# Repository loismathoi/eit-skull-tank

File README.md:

> [!WARNING]
> Work in progress. Incomplete and subject to change.

# Electrical Impedance Tomography Skull Phantom

16-electrode EIT system and FDM-printed head phantom, built to see how a skull analogue interacts with EIT imaging and ischemia detection.

## Goals
- How accurate is EIT on a 3D-printed, quasi-2D tank?
- How does the inclusion of a skull-ring impact measurement accuracy?
- Can a neural network improve accuracy and detectable inclusion size compared to GREIT?

## Repository

- [hardware/](hardware/): PCB and tank design files.
- [firmware/](firmware/): code that runs on the PCB.
- [sim/](sim/): simulation of the phantom.
- [img/](img/): images.
- [environment.yml](environment.yml): Python environment.

## System

- CALVA: the PCB, details in [hardware/README.md](hardware/README.md).
- Tank: 3D-printed, TODO.

## Status

- Done: PCB rev 1.0 designed and fabricated.
- Done: stock firmware builds, not flashed yet.
- Done: basic simulation of the tank with GREIT reconstruction (See  [here](/img/sim-greit-ring.png)).
- TODO: PCB assembly and bring-up.
- TODO: tank design and printing.
- Planning: data acquisition.
- Planning: neural network.

## Credits

- [CN0565](https://www.analog.com/en/resources/reference-designs/circuits-from-the-lab/CN0565.html), [EVAL-ADICUP3029](https://www.analog.com/en/resources/evaluation-hardware-and-software/evaluation-boards-kits/eval-adicup3029.html), [no-OS](https://github.com/analogdevicesinc/no-OS), [pyEIT](https://github.com/eitcom/pyEIT)

## License

- [hardware/](hardware/): CERN-OHL-P v2, see [hardware/LICENSE](hardware/LICENSE).
- [firmware/no-OS](https://github.com/loismathoi/no-OS/tree/calva): its own licenses, see [firmware/no-OS/COPYING](https://github.com/loismathoi/no-OS/blob/calva/COPYING).
- Everything else: MIT, see [LICENSE](LICENSE).

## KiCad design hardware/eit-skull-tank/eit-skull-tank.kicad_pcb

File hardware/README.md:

# HARDWARE

## CALVA

*Bare PCB*

- 16-electrode EIT board, rev 1.0, 4-layer, 100 x 51 mm.
- Electrode side isolated from the USB side, following CN0565.

## Based on

- [CN0565](https://www.analog.com/en/resources/reference-designs/circuits-from-the-lab/CN0565.html): AFE, mux, isolation, isolated power.
- [EVAL-ADICUP3029](https://www.analog.com/en/resources/evaluation-hardware-and-software/evaluation-boards-kits/eval-adicup3029.html): MCU, clocks, SWD, LEDs.

## Files

- [eit-skull-tank/](eit-skull-tank/): KiCad 10 project.
- [eit-skull-tank.pdf](eit-skull-tank.pdf): schematic.
- Sheets: [usb_power](eit-skull-tank/usb_power.kicad_sch), [mcu](eit-skull-tank/mcu.kicad_sch), [iso_power](eit-skull-tank/iso_power.kicad_sch), [iso_comm](eit-skull-tank/iso_comm.kicad_sch), [afe](eit-skull-tank/afe.kicad_sch), [mux](eit-skull-tank/mux.kicad_sch).

## Fabrication

- AISLER, 4-layer, 1.6 mm, ENIG, exported with the AISLER KiCad plugin.
- Stencil and hot plate reflow.

## Tank
### TODO

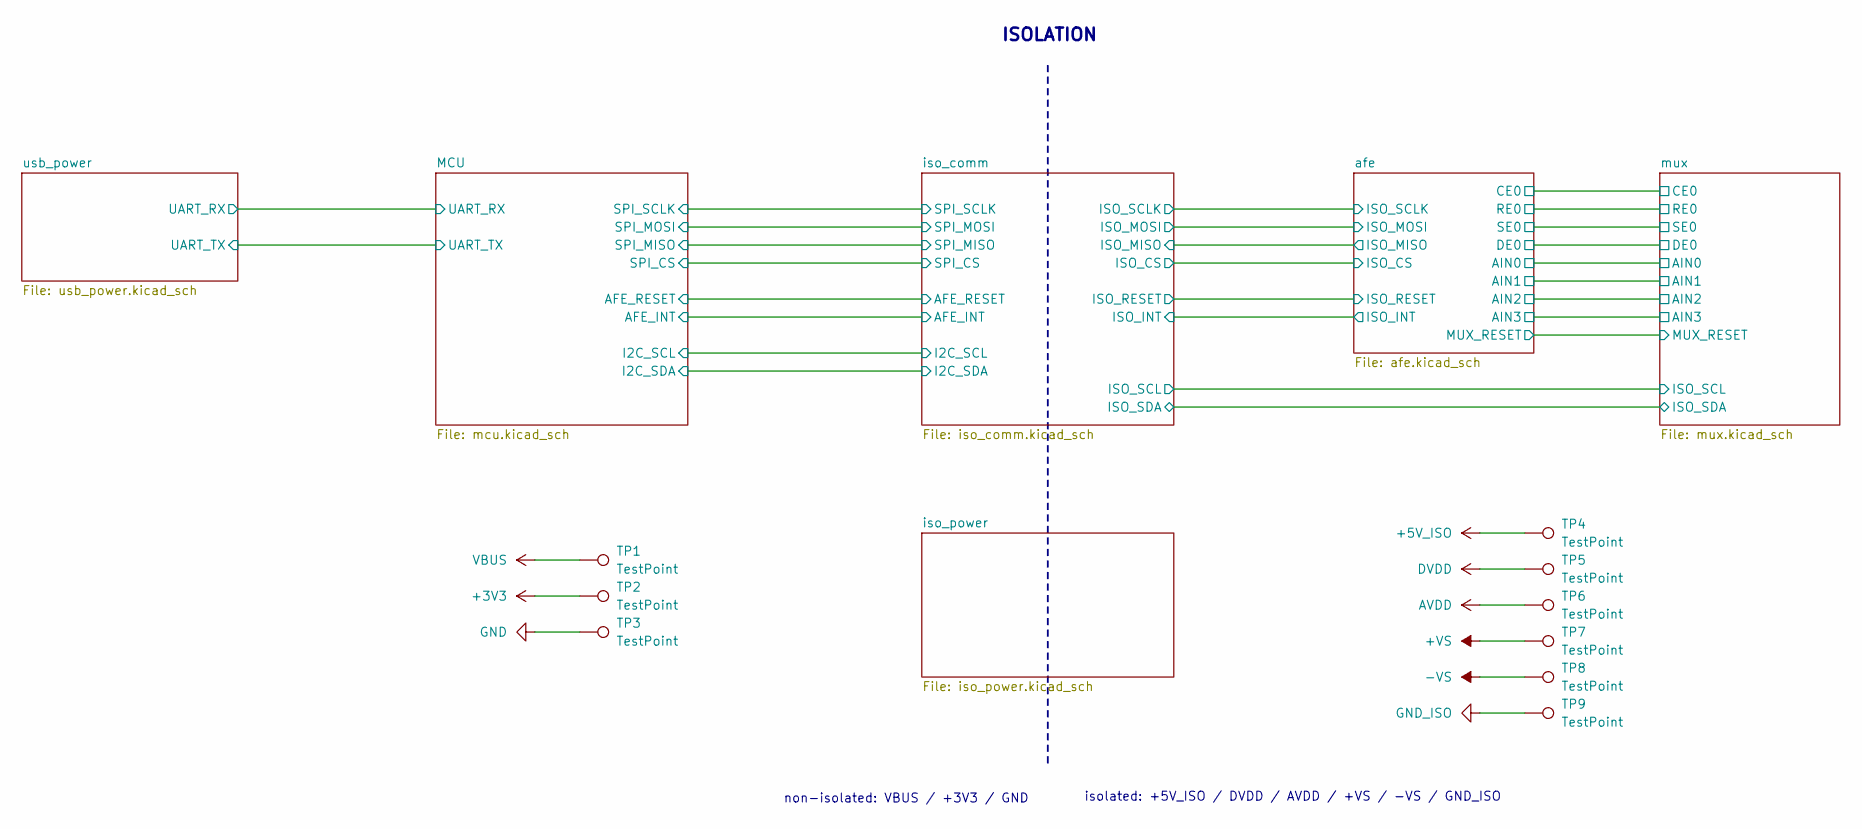
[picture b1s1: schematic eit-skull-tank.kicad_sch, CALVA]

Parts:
TP1, TP2, TP3, TP4, TP5, TP6, TP7, TP8, TP9: TestPoint; TestPoint_Pad_D1.5mm

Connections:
+3V3: TP2.1 (1_1); also elsewhere on the board
+5V_ISO: TP4.1 (1_1); also elsewhere on the board
+VS: TP7.1 (1_1); also elsewhere on the board
-VS: TP8.1 (1_1); also elsewhere on the board
AVDD: TP6.1 (1_1); also elsewhere on the board
DVDD: TP5.1 (1_1); also elsewhere on the board
GND: TP3.1 (1_1); also elsewhere on the board
GND_ISO: TP9.1 (1_1); also elsewhere on the board
VBUS: TP1.1 (1_1); also elsewhere on the board

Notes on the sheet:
isolated: +5V_ISO / DVDD / AVDD / +VS / -VS / GND_ISO
ISOLATION
non-isolated: VBUS / +3V3 / GND

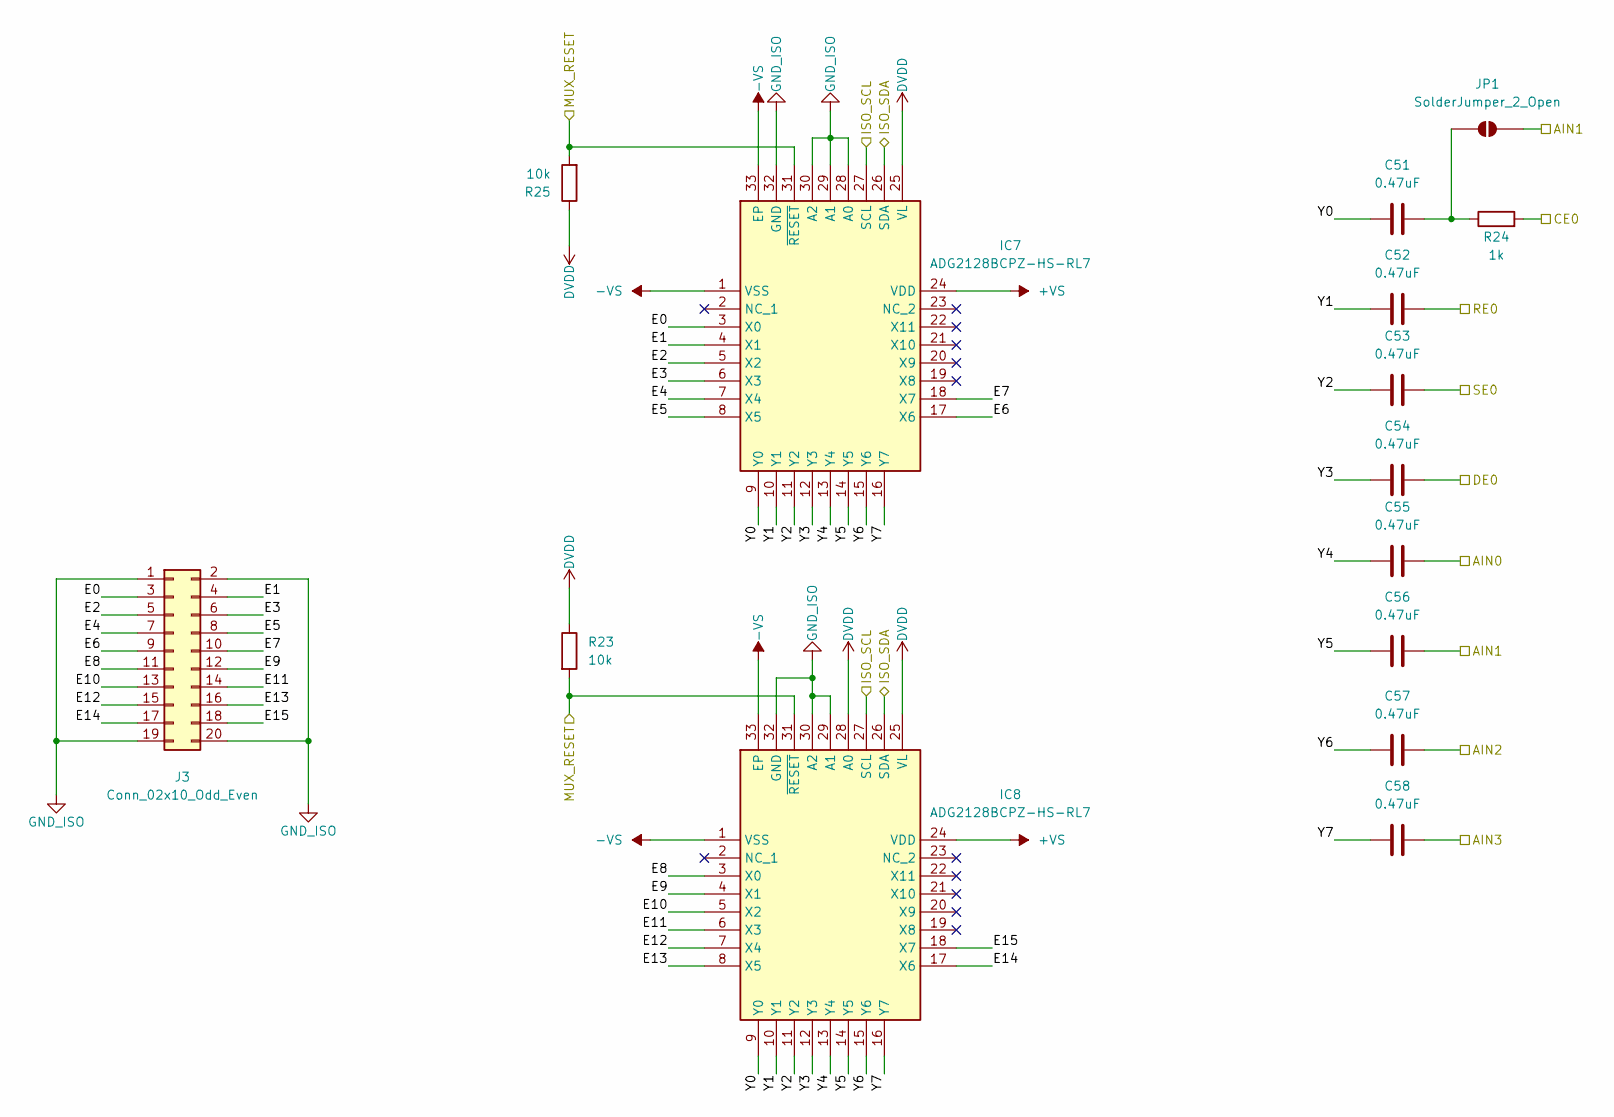
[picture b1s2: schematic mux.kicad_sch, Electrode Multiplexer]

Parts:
C51, C52, C53, C54, C55, C56, C57, C58: 0.47uF; C_0805_2012Metric; MPN CL21B474KAFNNNE
IC7, IC8: ADG2128BCPZ-HS-RL7; LFCSP-32-1EP_5x5mm_P0.5mm_EP3.25x3.25mm; MPN ADG2128BCPZ-HS-RL7
J3: Conn_02x10_Odd_Even; IDC-Header_2x10_P2.54mm_Vertical; MPN 61202021621
JP1: SolderJumper_2_Open; SolderJumper-2_P1.3mm_Open_RoundedPad1.0x1.5mm
R23, R25: 10k; R_0805_2012Metric; MPN RC0805FR-0710KL
R24: 1k; R_0805_2012Metric; MPN RC0805FR-071KL

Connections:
+VS: IC7.24 (VDD), IC8.24 (VDD); also elsewhere on the board
-VS: IC7.1 (VSS), IC7.33 (EP), IC8.1 (VSS), IC8.33 (EP); also elsewhere on the board
/afe/AIN0: C55.2; also elsewhere on the board
/afe/AIN1: C56.2, JP1.2 (B); also elsewhere on the board
/afe/AIN2: C57.2; also elsewhere on the board
/afe/AIN3: C58.2; also elsewhere on the board
/afe/CE0: R24.2; also elsewhere on the board
/afe/DE0: C54.2; also elsewhere on the board
/afe/MUX_RESET: IC7.31 (~RESET), IC8.31 (~RESET), R23.2, R25.2; also elsewhere on the board
/afe/RE0: C52.2; also elsewhere on the board
/afe/SE0: C53.2; also elsewhere on the board
/iso_comm/ISO_SCL: IC7.27 (SCL), IC8.27 (SCL); also elsewhere on the board
/iso_comm/ISO_SDA: IC7.26 (SDA), IC8.26 (SDA); also elsewhere on the board
/mux/E0: IC7.3 (X0), J3.3
/mux/E1: IC7.4 (X1), J3.4
/mux/E2: IC7.5 (X2), J3.5
/mux/E3: IC7.6 (X3), J3.6
/mux/E4: IC7.7 (X4), J3.7
/mux/E5: IC7.8 (X5), J3.8
/mux/E6: IC7.17 (X6), J3.9
/mux/E7: IC7.18 (X7), J3.10
/mux/E8: IC8.3 (X0), J3.11
/mux/E9: IC8.4 (X1), J3.12
/mux/E10: IC8.5 (X2), J3.13
/mux/E11: IC8.6 (X3), J3.14
/mux/E12: IC8.7 (X4), J3.15
/mux/E13: IC8.8 (X5), J3.16
/mux/E14: IC8.17 (X6), J3.17
/mux/E15: IC8.18 (X7), J3.18
/mux/Y0: C51.1, IC7.9 (Y0), IC8.9 (Y0)
/mux/Y1: C52.1, IC7.10 (Y1), IC8.10 (Y1)
/mux/Y2: C53.1, IC7.11 (Y2), IC8.11 (Y2)
/mux/Y3: C54.1, IC7.12 (Y3), IC8.12 (Y3)
/mux/Y4: C55.1, IC7.13 (Y4), IC8.13 (Y4)
/mux/Y5: C56.1, IC7.14 (Y5), IC8.14 (Y5)
/mux/Y6: C57.1, IC7.15 (Y6), IC8.15 (Y6)
/mux/Y7: C58.1, IC7.16 (Y7), IC8.16 (Y7)
DVDD: IC7.25 (VL), IC8.25 (VL), IC8.28 (A0), R23.1, R25.1; also elsewhere on the board
GND_ISO: IC7.28 (A0), IC7.29 (A1), IC7.30 (A2), IC7.32 (GND), IC8.29 (A1), IC8.30 (A2), IC8.32 (GND), J3.1, J3.2, J3.19, J3.20; also elsewhere on the board
unnamed: C51.2, JP1.1 (A), R24.1

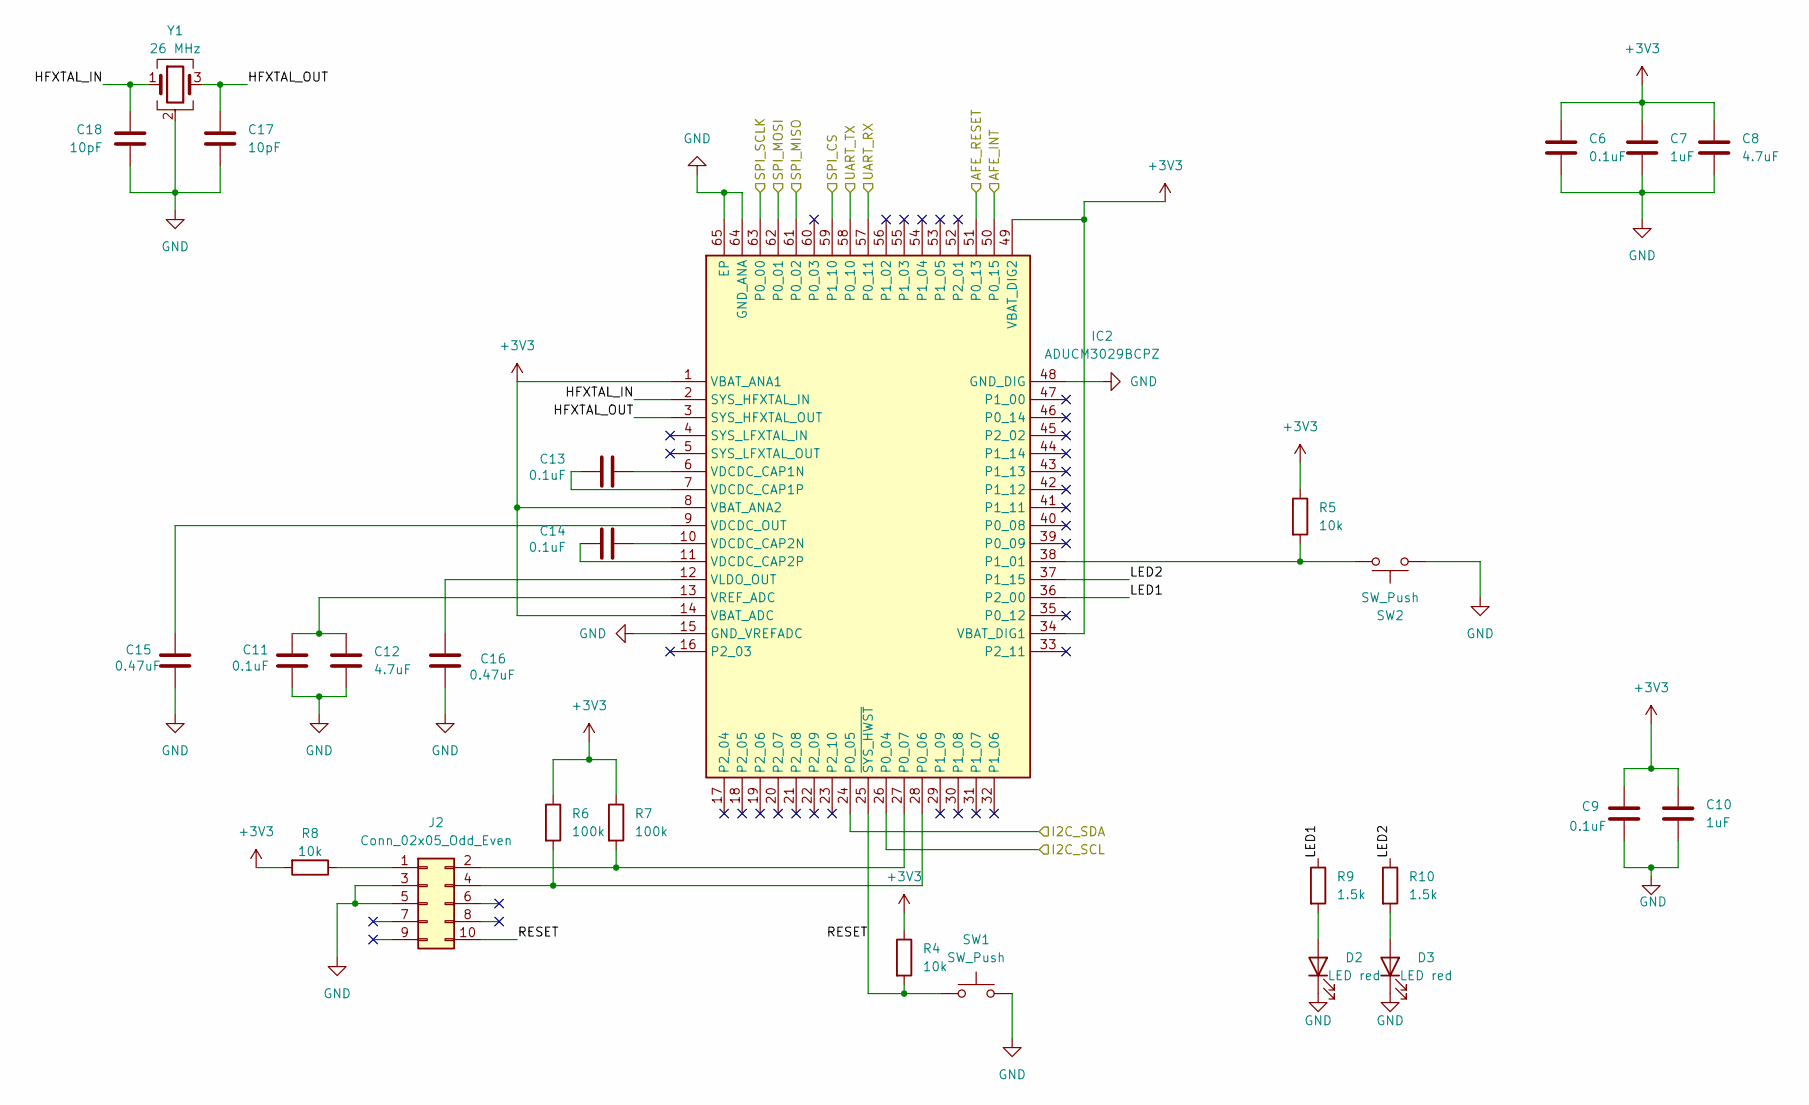
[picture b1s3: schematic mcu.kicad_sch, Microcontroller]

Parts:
C6, C9, C11, C13, C14: 0.1uF; C_0603_1608Metric; MPN CC0603KRX7R9BB104
C7, C10: 1uF; C_0603_1608Metric; MPN C1608X7R1E105K080AB
C8, C12: 4.7uF; C_0603_1608Metric; MPN CL10A475KA8NQNC
C15, C16: 0.47uF; C_0603_1608Metric; MPN GRM188R71C474KA88D
C17, C18: 10pF; C_0603_1608Metric; MPN CL10C100JB81PNC
D2, D3: LED red; LED_0805_2012Metric; MPN APT2012SURCK
IC2: ADUCM3029BCPZ; LFCSP-64-1EP_9x9mm_P0.5mm_EP4.6x4.6mm; MPN ADUCM3029BCPZ-R7
J2: Conn_02x05_Odd_Even; Samtec_FTSH-105-01-L-DV-K_2x05_P1.27mm; MPN FTSH-105-01-L-DV-K
R4, R5, R8: 10k; R_0805_2012Metric; MPN RC0805FR-0710KL
R6, R7: 100k; R_0805_2012Metric; MPN RC0805FR-07100KL
R9, R10: 1.5k; R_0805_2012Metric; MPN RC0805FR-071K5L
SW1, SW2: SW_Push; SW_SPST_PTS645Sx43SMTR92; MPN PTS645SM43SMTR92 LFS
Y1: 26 MHz; Crystal_SMD_3225-4Pin_3.2x2.5mm; MPN ECS-260-8-33-RWY-TR

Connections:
+3V3: C6.1, C7.1, C8.1, C9.1, C10.1, IC2.1 (VBAT_ANA1), IC2.8 (VBAT_ANA2), IC2.14 (VBAT_ADC), IC2.34 (VBAT_DIG1), IC2.49 (VBAT_DIG2), R4.1, R5.1, R6.1, R7.1, R8.2; also elsewhere on the board
/MCU/AFE_INT: IC2.50 (P0_15); also elsewhere on the board
/MCU/AFE_RESET: IC2.51 (P0_13); also elsewhere on the board
/MCU/HFXTAL_IN: C18.1, IC2.2 (SYS_HFXTAL_IN), Y1.1
/MCU/HFXTAL_OUT: C17.1, IC2.3 (SYS_HFXTAL_OUT), Y1.3
/MCU/I2C_SCL: IC2.26 (P0_04); also elsewhere on the board
/MCU/I2C_SDA: IC2.24 (P0_05); also elsewhere on the board
/MCU/LED1: IC2.36 (P2_00), R9.1
/MCU/LED2: IC2.37 (P1_15), R10.1
/MCU/RESET: IC2.25 (~SYS_HWST), J2.10, R4.2, SW1.1
/MCU/SPI_CS: IC2.59 (P1_10); also elsewhere on the board
/MCU/SPI_MISO: IC2.61 (P0_02); also elsewhere on the board
/MCU/SPI_MOSI: IC2.62 (P0_01); also elsewhere on the board
/MCU/SPI_SCLK: IC2.63 (P0_00); also elsewhere on the board
/MCU/UART_RX: IC2.57 (P0_11); also elsewhere on the board
/MCU/UART_TX: IC2.58 (P0_10); also elsewhere on the board
GND: C6.2, C7.2, C8.2, C9.2, C10.2, C11.2, C12.2, C15.2, C16.2, C17.2, C18.2, D2.1 (K), D3.1 (K), IC2.15 (GND_VREFADC), IC2.48 (GND_DIG), IC2.64 (GND_ANA), IC2.65 (EP), J2.3, J2.5, SW1.2, SW2.1, Y1.2 (G), Y1.4 (G); also elsewhere on the board
unnamed: D2.2 (A), R9.2
unnamed: D3.2 (A), R10.2
unnamed: IC2.28 (P0_06), J2.4, R6.2
unnamed: IC2.27 (P0_07), J2.2, R7.2
unnamed: IC2.38 (P1_01), R5.2, SW2.2
unnamed: C13.1, IC2.6 (VDCDC_CAP1N)
unnamed: C13.2, IC2.7 (VDCDC_CAP1P)
unnamed: C14.1, IC2.10 (VDCDC_CAP2N)
unnamed: C14.2, IC2.11 (VDCDC_CAP2P)
unnamed: C15.1, IC2.9 (VDCDC_OUT)
unnamed: C16.1, IC2.12 (VLDO_OUT)
unnamed: C11.1, C12.1, IC2.13 (VREF_ADC)
unnamed: J2.1, R8.1

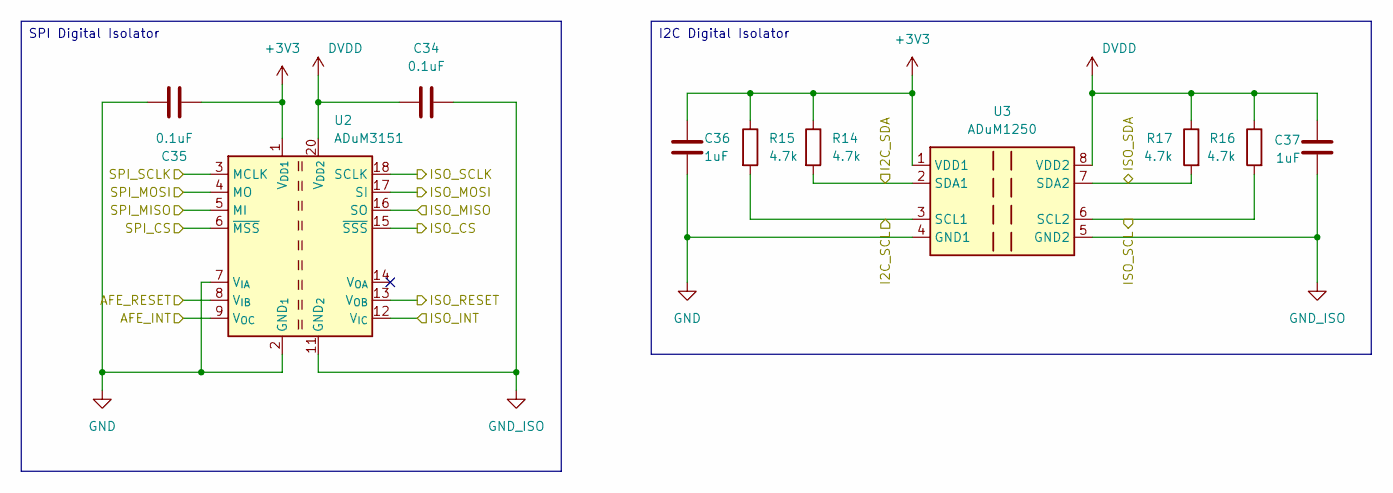
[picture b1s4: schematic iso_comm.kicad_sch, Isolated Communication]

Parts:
C34, C35: 0.1uF; C_0805_2012Metric; MPN CL21B104KBCNNNC
C36, C37: 1uF; C_0805_2012Metric; MPN C0805C105K5RACTU
R14, R15, R16, R17: 4.7k; R_0805_2012Metric; MPN RC0805FR-074K7L
U2: ADuM3151; SSOP-20_5.3x7.2mm_P0.65mm; MPN ADUM3151BRSZ
U3: ADuM1250; SOIC-8_3.9x4.9mm_P1.27mm; MPN ADUM1250ARZ

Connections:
+3V3: C35.2, C36.1, R14.1, R15.1, U2.1 (V_{DD1}), U3.1 (VDD1); also elsewhere on the board
/MCU/AFE_INT: U2.9 (V_{OC}); also elsewhere on the board
/MCU/AFE_RESET: U2.8 (V_{IB}); also elsewhere on the board
/MCU/I2C_SCL: R15.2, U3.3 (SCL1); also elsewhere on the board
/MCU/I2C_SDA: R14.2, U3.2 (SDA1); also elsewhere on the board
/MCU/SPI_CS: U2.6 (~MSS); also elsewhere on the board
/MCU/SPI_MISO: U2.5 (MI); also elsewhere on the board
/MCU/SPI_MOSI: U2.4 (MO); also elsewhere on the board
/MCU/SPI_SCLK: U2.3 (MCLK); also elsewhere on the board
/afe/ISO_CS: U2.15 (~SSS); also elsewhere on the board
/afe/ISO_INT: U2.12 (V_{IC}); also elsewhere on the board
/afe/ISO_MISO: U2.16 (SO); also elsewhere on the board
/afe/ISO_MOSI: U2.17 (SI); also elsewhere on the board
/afe/ISO_RESET: U2.13 (V_{OB}); also elsewhere on the board
/afe/ISO_SCLK: U2.18 (SCLK); also elsewhere on the board
/iso_comm/ISO_SCL: R16.2, U3.6 (SCL2); also elsewhere on the board
/iso_comm/ISO_SDA: R17.2, U3.7 (SDA2); also elsewhere on the board
DVDD: C34.2, C37.1, R16.1, R17.1, U2.20 (V_{DD2}), U3.8 (VDD2); also elsewhere on the board
GND: C35.1, C36.2, U2.2 (GND_{1}), U2.7 (V_{IA}), U2.10 (GND_{1}), U3.4 (GND1); also elsewhere on the board
GND_ISO: C34.1, C37.2, U2.11 (GND_{2}), U2.19 (GND_{2}), U3.5 (GND2); also elsewhere on the board

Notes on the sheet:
SPI Digital Isolator
I2C Digital Isolator

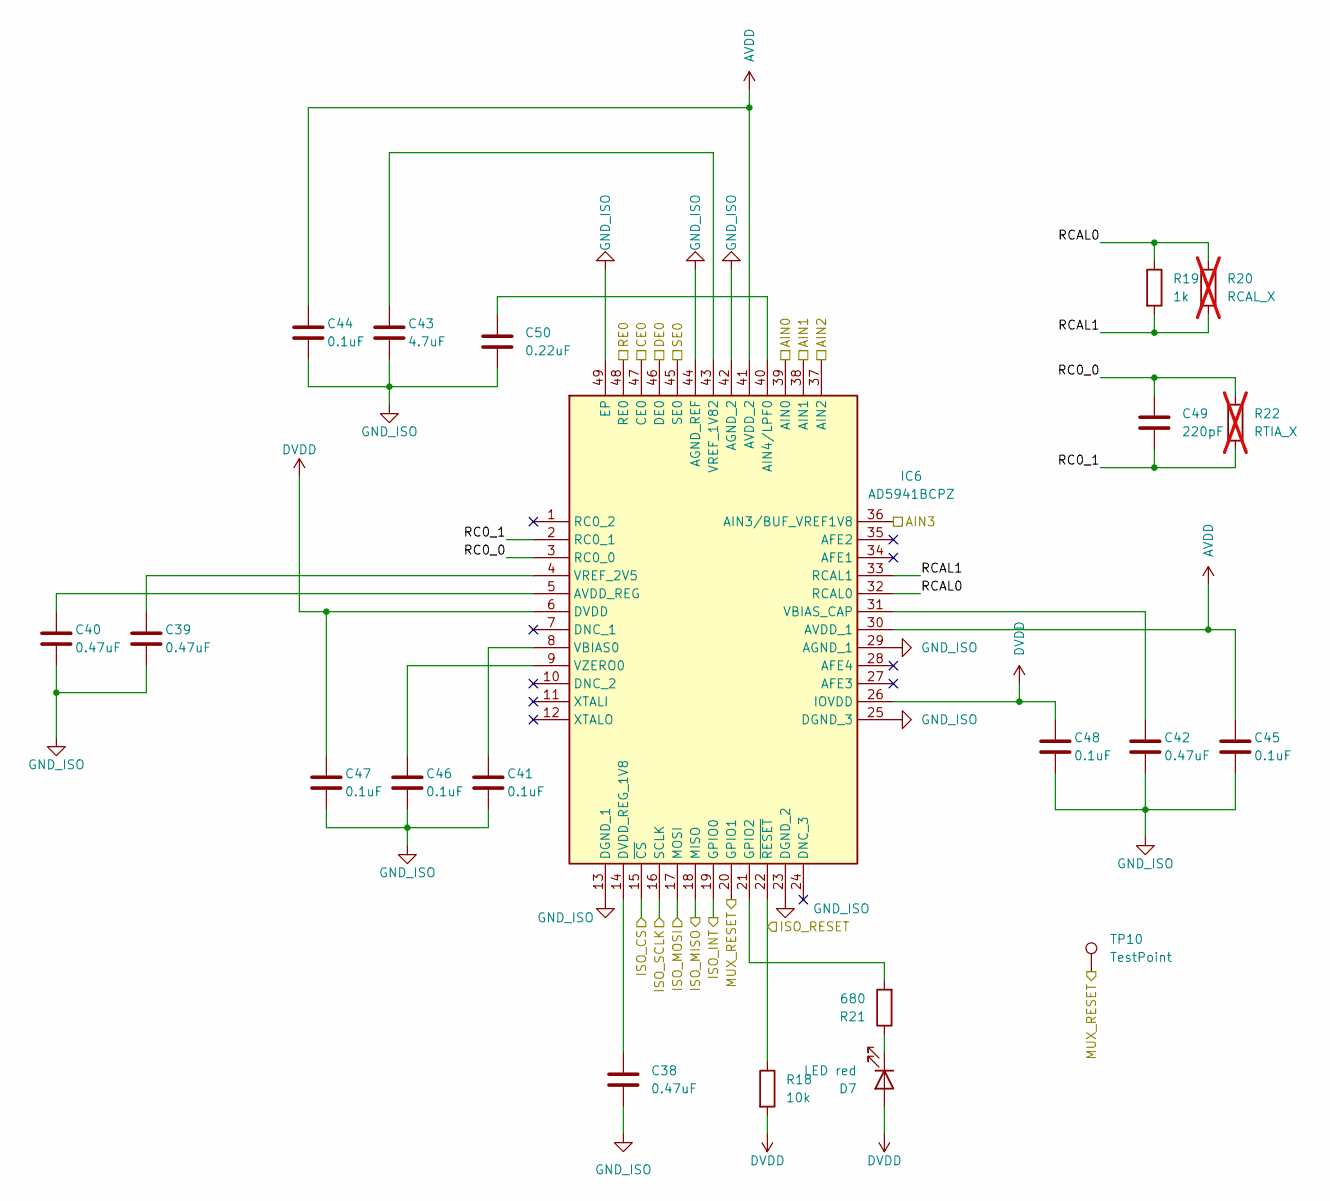
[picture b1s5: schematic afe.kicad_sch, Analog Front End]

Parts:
C38, C39, C40, C42: 0.47uF; C_0603_1608Metric; MPN GRM188R71C474KA88D
C41, C44, C45, C46, C47, C48: 0.1uF; C_0603_1608Metric; MPN CC0603KRX7R9BB104
C43: 4.7uF; C_0603_1608Metric; MPN CL10A475KA8NQNC
C49: 220pF; C_0603_1608Metric; MPN CL10C221JB8NNNC
C50: 0.22uF; C_0603_1608Metric; MPN CL10B224KA8NNNC
D7: LED red; LED_0805_2012Metric; MPN APT2012SURCK
IC6: AD5941BCPZ; LFCSP-48-1EP_7x7mm_P0.5mm_EP5.2x5.2mm; MPN AD5941BCPZ
R18: 10k; R_0805_2012Metric; MPN RC0805FR-0710KL
R19: 1k; R_0805_2012Metric; MPN RC0805FR-071KL
R20: RCAL_X; R_0805_2012Metric; not fitted
R21: 680; R_0805_2012Metric; MPN RC0805FR-07680RL
R22: RTIA_X; R_0805_2012Metric; not fitted
TP10: TestPoint; TestPoint_Pad_D1.5mm

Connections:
/afe/AIN0: IC6.39 (AIN0); also elsewhere on the board
/afe/AIN1: IC6.38 (AIN1); also elsewhere on the board
/afe/AIN2: IC6.37 (AIN2); also elsewhere on the board
/afe/AIN3: IC6.36 (AIN3/BUF_VREF1V8); also elsewhere on the board
/afe/CE0: IC6.47 (CE0); also elsewhere on the board
/afe/DE0: IC6.46 (DE0); also elsewhere on the board
/afe/ISO_CS: IC6.15 (~CS); also elsewhere on the board
/afe/ISO_INT: IC6.19 (GPIO0); also elsewhere on the board
/afe/ISO_MISO: IC6.18 (MISO); also elsewhere on the board
/afe/ISO_MOSI: IC6.17 (MOSI); also elsewhere on the board
/afe/ISO_RESET: IC6.22 (~RESET), R18.1; also elsewhere on the board
/afe/ISO_SCLK: IC6.16 (SCLK); also elsewhere on the board
/afe/MUX_RESET: IC6.20 (GPIO1), TP10.1 (1_1); also elsewhere on the board
/afe/RC0_0: C49.1, IC6.3 (RC0_0), R22.1
/afe/RC0_1: C49.2, IC6.2 (RC0_1), R22.2
/afe/RCAL0: IC6.32 (RCAL0), R19.1, R20.1
/afe/RCAL1: IC6.33 (RCAL1), R19.2, R20.2
/afe/RE0: IC6.48 (RE0); also elsewhere on the board
/afe/SE0: IC6.45 (SE0); also elsewhere on the board
AVDD: C44.1, C45.1, IC6.30 (AVDD_1), IC6.41 (AVDD_2); also elsewhere on the board
DVDD: C47.1, C48.1, D7.2 (A), IC6.6 (DVDD), IC6.26 (IOVDD), R18.2; also elsewhere on the board
GND_ISO: C38.2, C39.2, C40.2, C41.2, C42.2, C43.2, C44.2, C45.2, C46.2, C47.2, C48.2, C50.2, IC6.13 (DGND_1), IC6.23 (DGND_2), IC6.25 (DGND_3), IC6.29 (AGND_1), IC6.42 (AGND_2), IC6.44 (AGND_REF), IC6.49 (EP); also elsewhere on the board
unnamed: D7.1 (K), R21.1
unnamed: C50.1, IC6.40 (AIN4/LPF0)
unnamed: C40.1, IC6.5 (AVDD_REG)
unnamed: C38.1, IC6.14 (DVDD_REG_1V8)
unnamed: IC6.21 (GPIO2), R21.2
unnamed: C41.1, IC6.8 (VBIAS0)
unnamed: C42.1, IC6.31 (VBIAS_CAP)
unnamed: C43.1, IC6.43 (VREF_1V82)
unnamed: C39.1, IC6.4 (VREF_2V5)
unnamed: C46.1, IC6.9 (VZERO0)

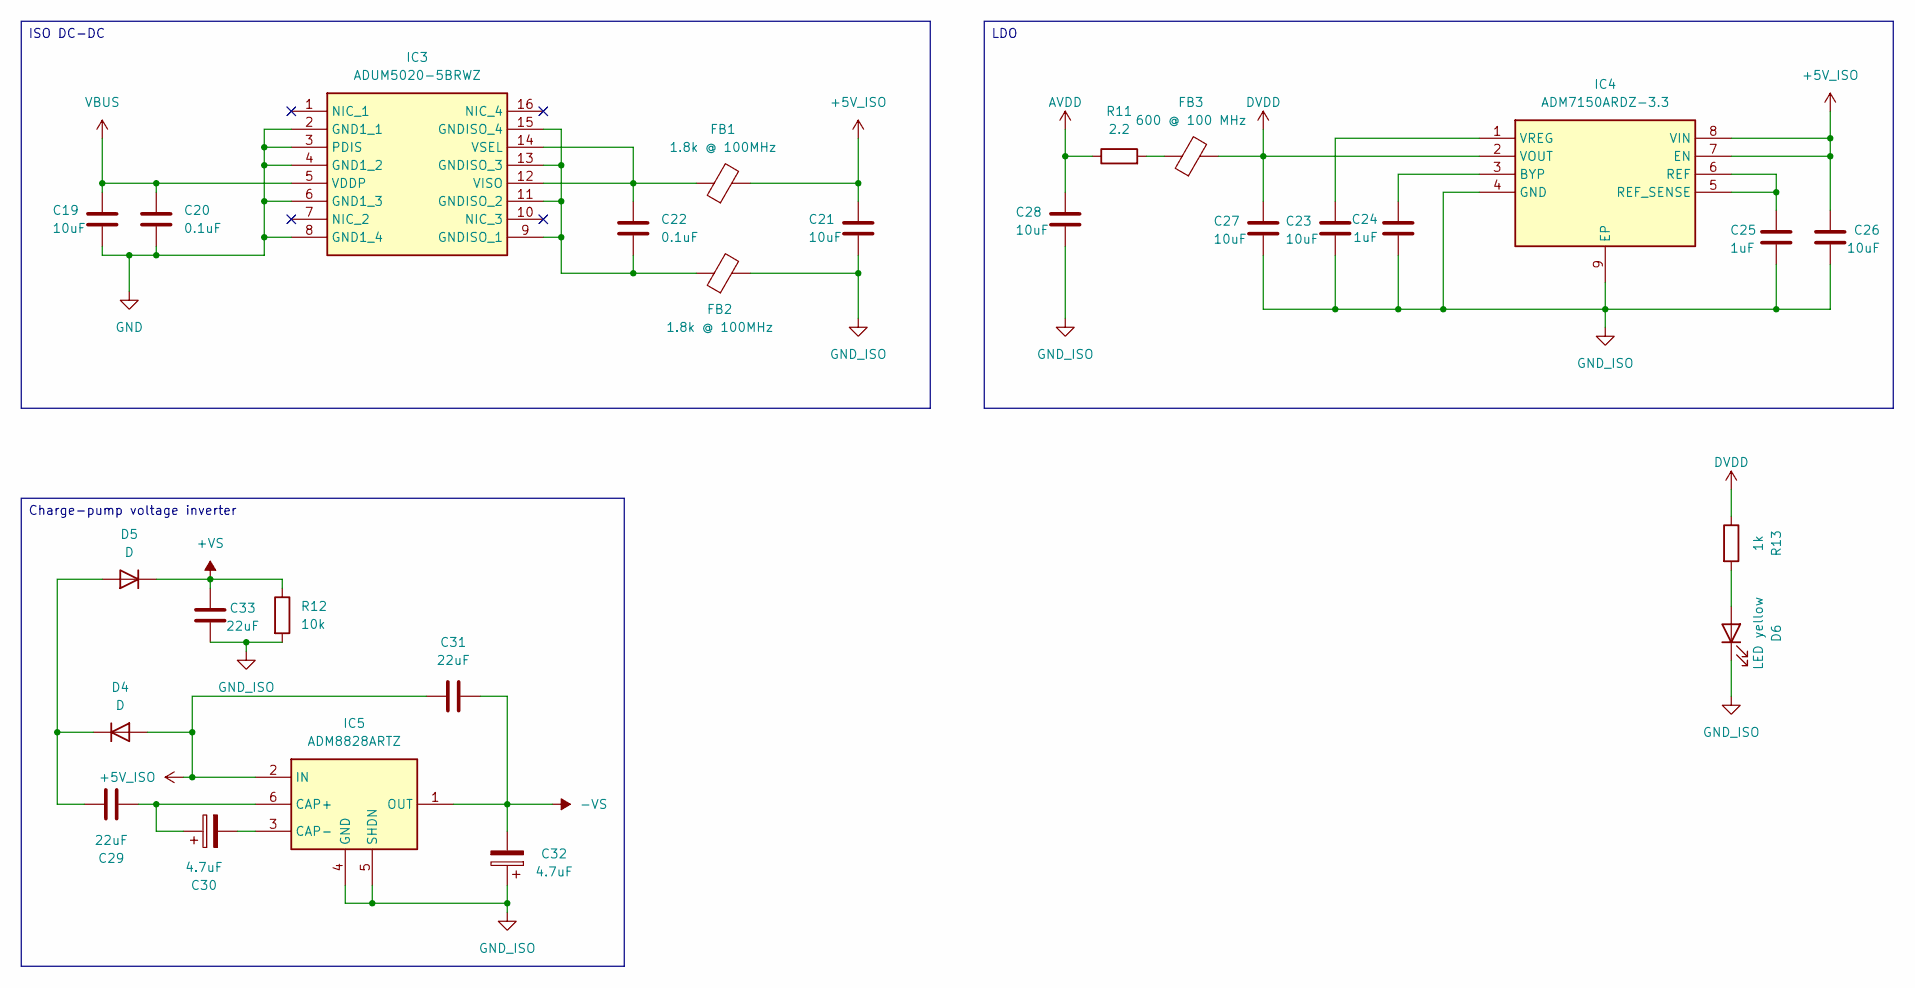
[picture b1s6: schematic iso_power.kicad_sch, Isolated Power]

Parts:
C19, C21, C23, C26, C27, C28: 10uF; C_0805_2012Metric; MPN C2012X5R1E106M125AB
C20, C22: 0.1uF; C_0805_2012Metric; MPN CL21B104KBCNNNC
C24, C25: 1uF; C_0805_2012Metric; MPN C0805C105K5RACTU
C29, C31, C33: 22uF; C_1206_3216Metric; MPN 12063D226KAT2A
C30, C32: 4.7uF; CP_EIA-2012-12_Kemet-R; MPN T55P475M010C0500
D4, D5: D; D_SOD-123; MPN 1N4148W-7-F
D6: LED yellow; LED_0805_2012Metric; MPN APT2012SYCK
FB1, FB2: 1.8k @ 100MHz; L_0402_1005Metric; MPN BLM15HD182SN1D
FB3: 600 @ 100 MHz; L_0603_1608Metric; MPN MPZ1608S601ATA00
IC3: ADUM5020-5BRWZ; SOIC-16W_7.5x10.3mm_P1.27mm; MPN ADUM5020-5BRWZ
IC4: ADM7150ARDZ-3.3; SOIC-8-1EP_3.9x4.9mm_P1.27mm_EP2.41x3.098mm; MPN ADM7150ARDZ-3.3-R7
IC5: ADM8828ARTZ; SOT-23-6; MPN ADM8828ARTZ-REEL7
R11: 2.2; R_0805_2012Metric; MPN RMCF0805FT2R20
R12: 10k; R_0805_2012Metric; MPN RC0805FR-0710KL
R13: 1k; R_0805_2012Metric; MPN RC0805FR-071KL

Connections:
+5V_ISO: C21.1, C26.1, C31.2, D4.2 (A), FB1.2, IC4.7 (EN), IC4.8 (VIN), IC5.2 (IN); also elsewhere on the board
+VS: C33.1, D5.1 (K), R12.1; also elsewhere on the board
-VS: C31.1, C32.2, IC5.1 (OUT); also elsewhere on the board
AVDD: C28.1, R11.1; also elsewhere on the board
DVDD: C27.1, FB3.2, IC4.2 (VOUT), R13.1; also elsewhere on the board
GND: C19.2, C20.2, IC3.2 (GND1_1), IC3.3 (PDIS), IC3.4 (GND1_2), IC3.6 (GND1_3), IC3.8 (GND1_4); also elsewhere on the board
GND_ISO: C21.2, C23.2, C24.2, C25.2, C26.2, C27.2, C28.2, C32.1, C33.2, D6.1 (K), FB2.2, IC4.4 (GND), IC4.9 (EP), IC5.4 (GND), IC5.5 (SHDN), R12.2; also elsewhere on the board
unnamed: C29.2, D4.1 (K), D5.2 (A)
unnamed: D6.2 (A), R13.2
unnamed: FB3.1, R11.2
unnamed: C22.2, FB2.1, IC3.9 (GNDISO_1), IC3.11 (GNDISO_2), IC3.13 (GNDISO_3), IC3.15 (GNDISO_4)
unnamed: C22.1, FB1.1, IC3.12 (VISO), IC3.14 (VSEL)
unnamed: C24.1, IC4.3 (BYP)
unnamed: C25.1, IC4.5 (REF_SENSE), IC4.6 (REF)
unnamed: C23.1, IC4.1 (VREG)
unnamed: C29.1, C30.1, IC5.6 (CAP+)
unnamed: C30.2, IC5.3 (CAP-)
VBUS: C19.1, C20.1, IC3.5 (VDDP); also elsewhere on the board

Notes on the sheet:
ISO DC-DC
LDO
Charge-pump voltage inverter

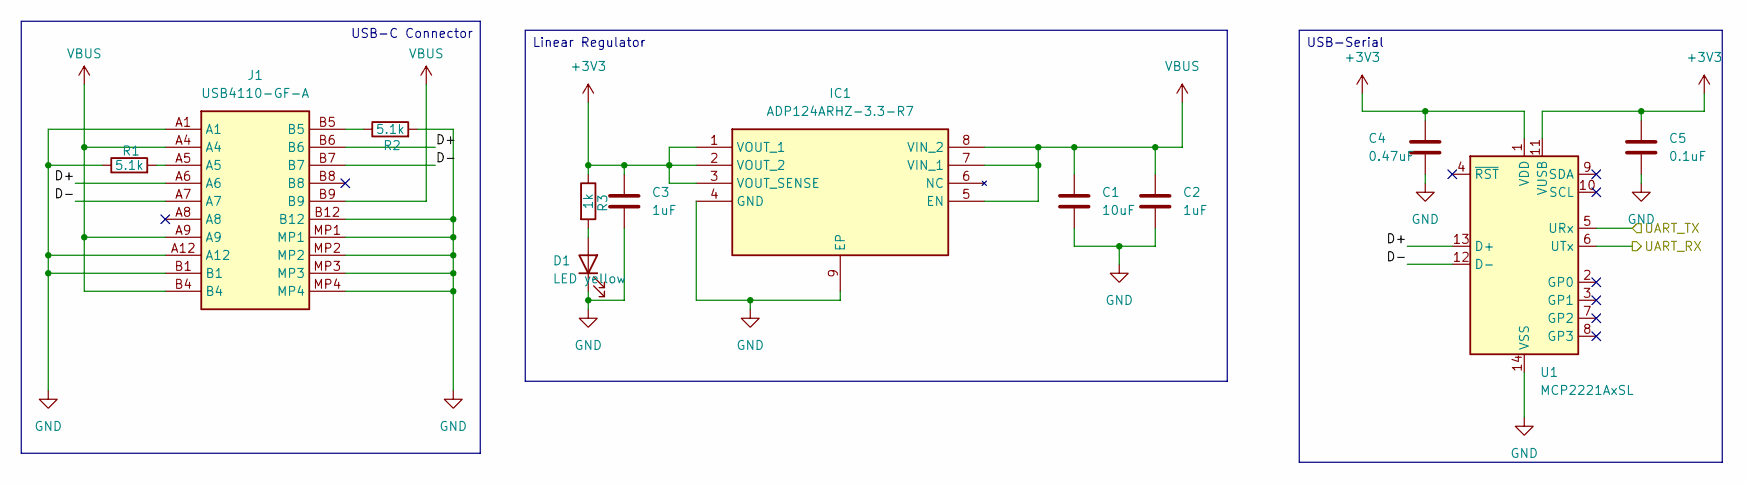
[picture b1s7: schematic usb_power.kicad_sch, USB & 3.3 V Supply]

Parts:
C1: 10uF; C_0805_2012Metric; MPN C2012X5R1E106M125AB
C2, C3: 1uF; C_0805_2012Metric; MPN C0805C105K5RACTU
C4: 0.47uF; C_0805_2012Metric; MPN CL21B474KAFNNNE
C5: 0.1uF; C_0805_2012Metric; MPN CL21B104KBCNNNC
D1: LED yellow; LED_0805_2012Metric; MPN APT2012SYCK
IC1: ADP124ARHZ-3.3-R7; MSOP-8-1EP_3x3mm_P0.65mm_EP1.76x1.825mm; MPN ADP124ARHZ-3.3-R7
J1: USB4110-GF-A; USB4110GFA_AISLER; MPN USB4110-GF-A
R1, R2: 5.1k; R_0805_2012Metric; MPN RC0805FR-075K1L
R3: 1k; R_0805_2012Metric; MPN RC0805FR-071KL
U1: MCP2221AxSL; SOIC-14_3.9x8.7mm_P1.27mm; MPN MCP2221A-I/SL

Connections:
+3V3: C3.1, C4.1, C5.1, IC1.1 (VOUT_1), IC1.2 (VOUT_2), IC1.3 (VOUT_SENSE), R3.1, U1.1 (VDD), U1.11 (VUSB); also elsewhere on the board
/MCU/UART_RX: U1.6 (UTx); also elsewhere on the board
/MCU/UART_TX: U1.5 (URx); also elsewhere on the board
/usb_power/D+: J1.A6, J1.B6, U1.13 (D+)
/usb_power/D-: J1.A7, J1.B7, U1.12 (D-)
GND: C1.2, C2.2, C3.2, C4.2, C5.2, D1.1 (K), IC1.4 (GND), IC1.9 (EP), J1.A1, J1.A12, J1.B1, J1.B12, J1.MP1, J1.MP2, J1.MP3, J1.MP4, R1.1, R2.2, U1.14 (VSS); also elsewhere on the board
unnamed: D1.2 (A), R3.2
unnamed: J1.A5, R1.2
unnamed: J1.B5, R2.1
VBUS: C1.1, C2.1, IC1.5 (EN), IC1.7 (VIN_1), IC1.8 (VIN_2), J1.A4, J1.A9, J1.B4, J1.B9; also elsewhere on the board

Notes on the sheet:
USB-Serial
USB-C Connector
Linear Regulator

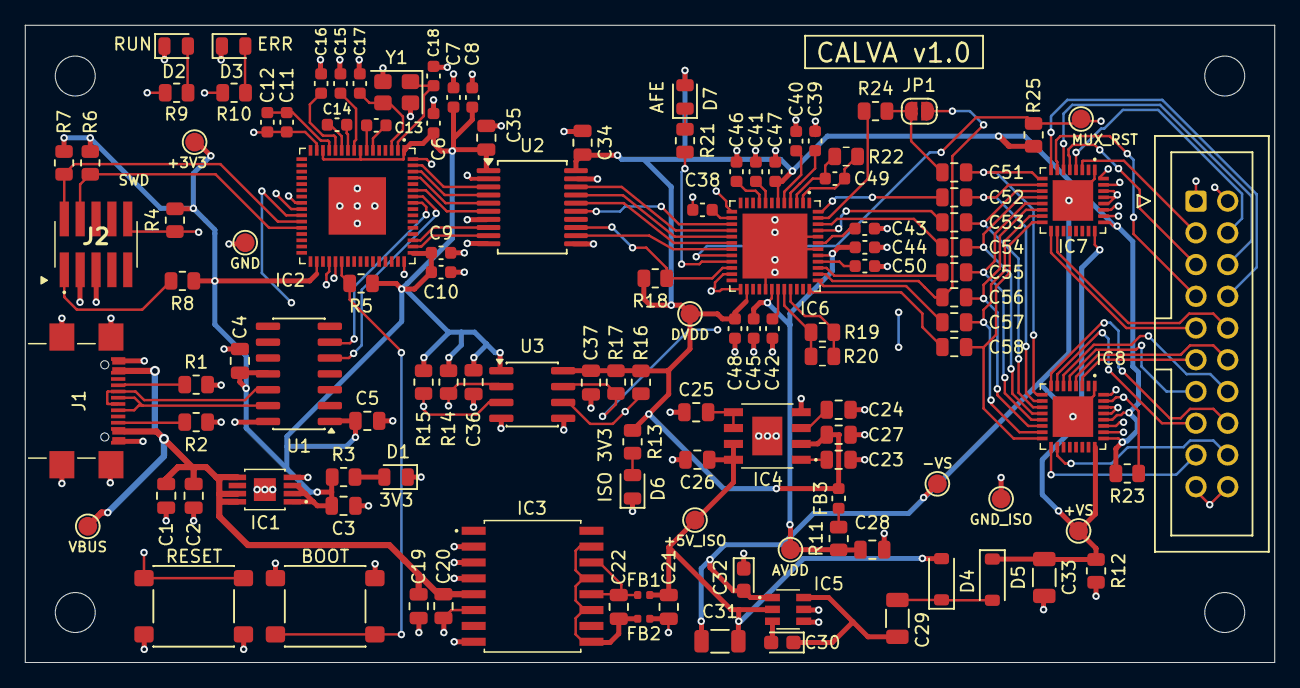
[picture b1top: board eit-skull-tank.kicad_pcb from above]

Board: 4 copper layers, 100.0 x 51.0 mm, 125 parts (0 on the bottom side), 108 nets.

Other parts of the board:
H1, H2, H3, H4: MountingHole_3.2mm_M3

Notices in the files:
hardware/eit-skull-tank/afe.kicad_sch:
Copyright 2026 Lois Mathoi. Licensed under CERN-OHL-P v2, https://cern.ch/cern-ohl
